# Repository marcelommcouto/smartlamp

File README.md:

# smartlamp
Projeto de lampada inteligente conectada a AWS

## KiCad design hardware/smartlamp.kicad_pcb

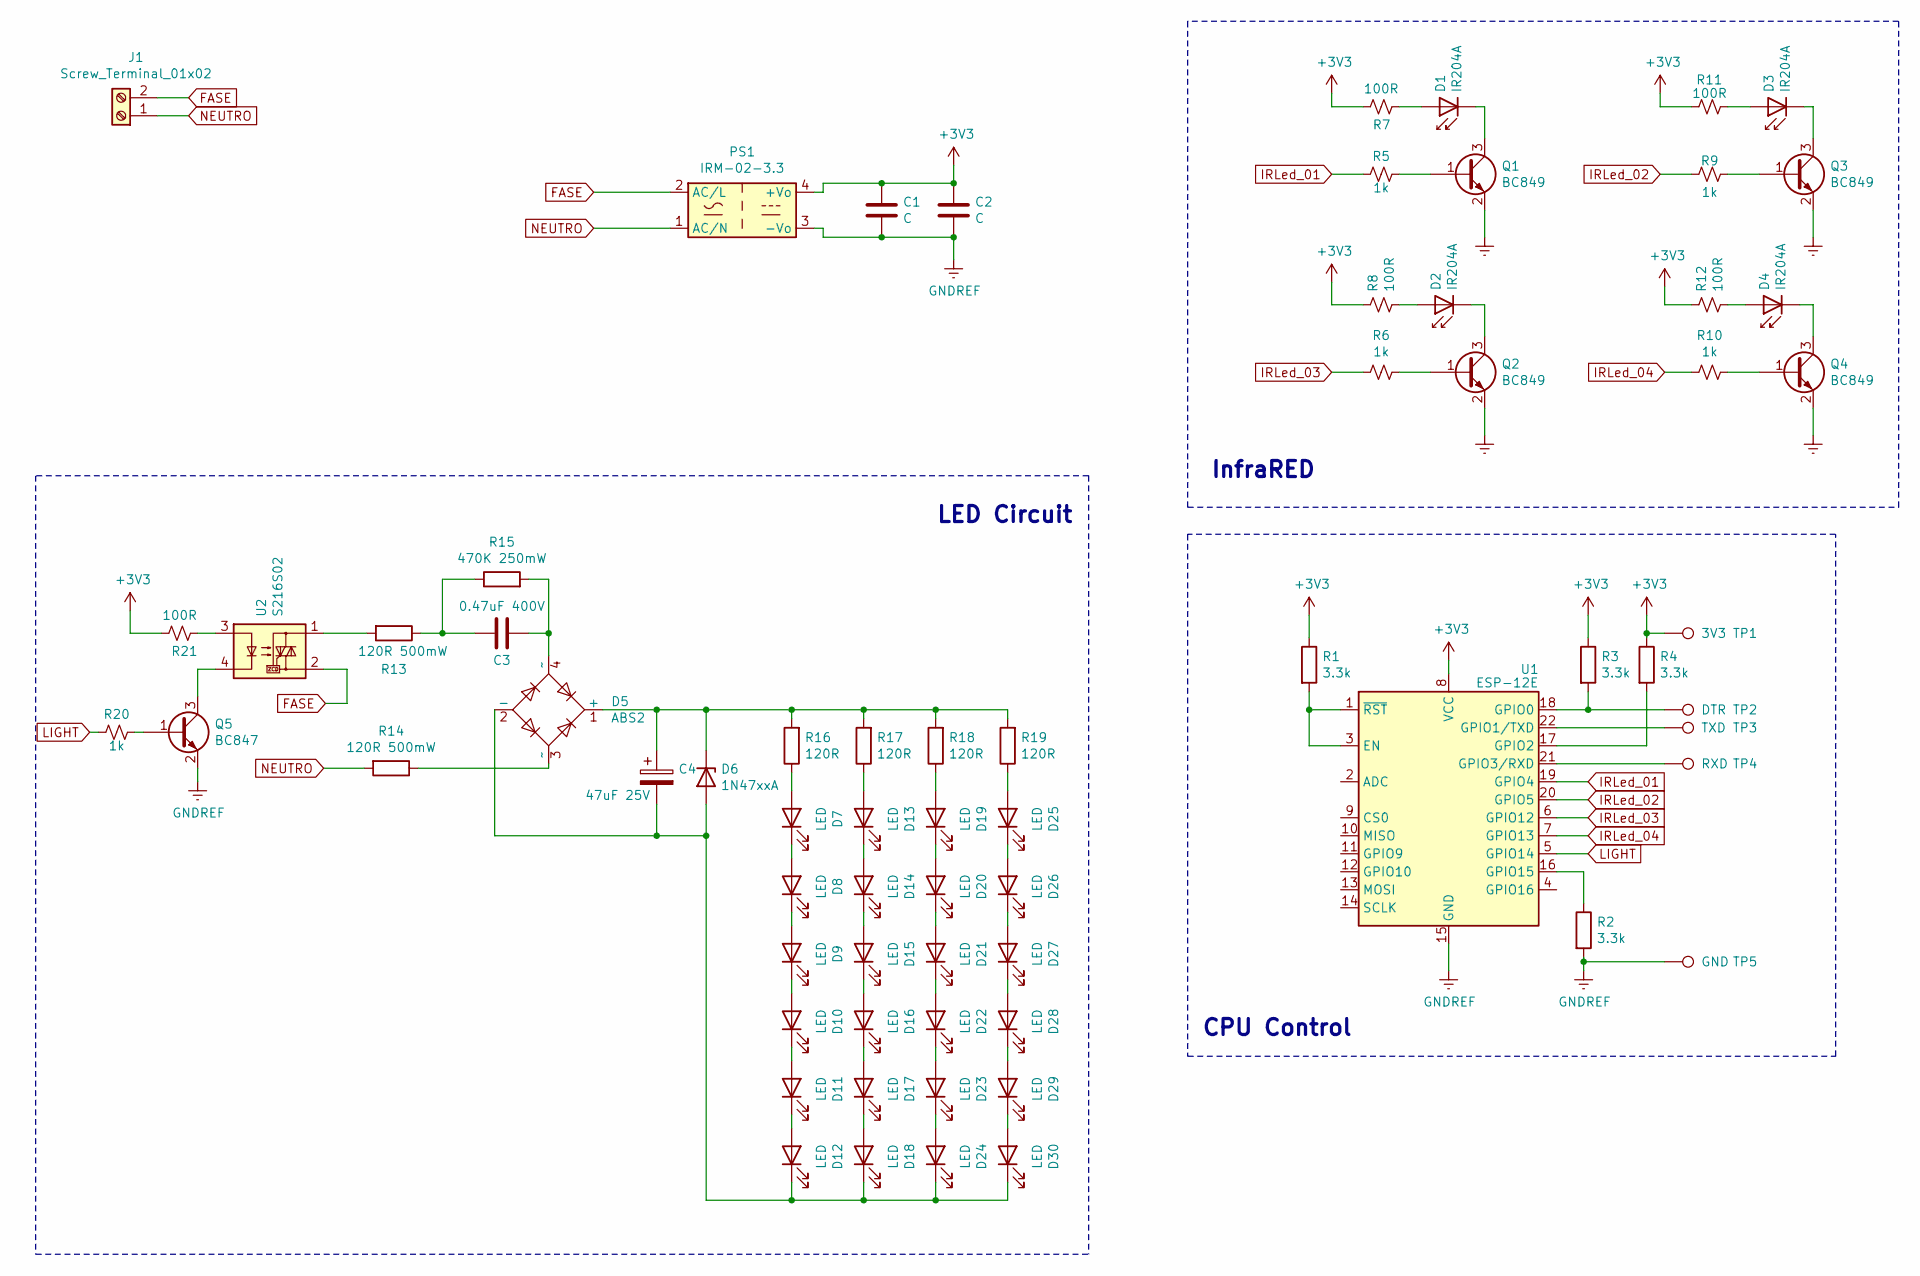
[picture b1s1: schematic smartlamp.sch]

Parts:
C1, C2: C; C_0805_2012Metric_Pad1.15x1.40mm_HandSolder
C3: 0.47uF 400V; C_Rect_L18.0mm_W8.0mm_P15.00mm_FKS3_FKP3
C4: 47uF 25V; C_Radial_D6.3mm_H11.0mm_P2.50mm
D1, D2, D3, D4: IR204A; LED_D3.0mm_IRBlack
D5: ABS2; Diode_Bridge_Diotec_ABS
D6: 1N47xxA; D_DO-41_SOD81_P10.16mm_Horizontal
D7, D8, D9, D10, D11, D12, D13, D14, D15, D16, D17, D18, D19, D20, D21, D22, D23, D24, D25, D26, D27, D28, D29, D30: LED; LED_1806_4516Metric
J1: Screw_Terminal_01x02; PhoenixContact_MCV_1,5_2-G-3.5_1x02_P3.50mm_Vertical
PS1: IRM-02-3.3; Converter_ACDC_MeanWell_IRM-02-xx_THT
Q1, Q2, Q3, Q4: BC849; SOT-23
Q5: BC847; SOT-23
R1, R2, R3, R4: 3.3k; C_0805_2012Metric_Pad1.15x1.40mm_HandSolder
R5, R6, R9, R10, R20: 1k; R_0805_2012Metric_Pad1.15x1.40mm_HandSolder
R7, R8, R11, R12, R21: 100R; R_0805_2012Metric_Pad1.15x1.40mm_HandSolder
R13, R14: 120R 500mW; R_1206_3216Metric_Pad1.42x1.75mm_HandSolder
R15: 470K 250mW; R_1206_3216Metric_Pad1.42x1.75mm_HandSolder
R16, R17, R18, R19: 120R; R_1206_3216Metric_Pad1.42x1.75mm_HandSolder
TP1: 3V3; TestPoint_Pad_D1.0mm
TP2: DTR; TestPoint_Pad_D1.0mm
TP3: TXD; TestPoint_Pad_D1.0mm
TP4: RXD; TestPoint_Pad_D1.0mm
TP5: GND; TestPoint_Pad_D1.0mm
U1: ESP-12E
U2: S216S02; SIP4_Sharp-SSR_P7.62mm_Straight

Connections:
+3V3: C1.1, C2.1, PS1.4 (+Vo), R1.1, R3.1, R4.1, R7.2, R8.1, R11.1, R12.1, R21.2, TP1.1, U1.8 (VCC)
FASE: J1.2, PS1.2 (AC/L), U2.2
GNDREF: C1.2, C2.2, PS1.3 (-Vo), Q1.2 (E), Q2.2 (E), Q3.2 (E), Q4.2 (E), Q5.2 (E), R2.2, TP5.1, U1.15 (GND)
IRLed_01: R5.2, U1.19 (GPIO4)
IRLed_02: R9.2, U1.20 (GPIO5)
IRLed_03: R6.2, U1.6 (GPIO12)
IRLed_04: R10.2, U1.7 (GPIO13)
LIGHT: R20.2, U1.5 (GPIO14)
NEUTRO: J1.1, PS1.1 (AC/N), R14.2
unnamed: C3.1, D5.4 (~~), R15.2
unnamed: C3.2, R13.1, R15.1
unnamed: C4.1, D5.1 (+), D6.1 (K), R16.2, R17.2, R18.2, R19.2
unnamed: C4.2, D5.2 (-), D6.2 (A), D12.1 (K), D18.1 (K), D24.1 (K), D30.1 (K)
unnamed: D1.1 (K), Q1.3 (C)
unnamed: D1.2 (A), R7.1
unnamed: D2.1 (K), Q2.3 (C)
unnamed: D2.2 (A), R8.2
unnamed: D3.1 (K), Q3.3 (C)
unnamed: D3.2 (A), R11.2
unnamed: D4.1 (K), Q4.3 (C)
unnamed: D4.2 (A), R12.2
unnamed: D5.3 (~~), R14.1
unnamed: D7.1 (K), D8.2 (A)
unnamed: D7.2 (A), R16.1
unnamed: D8.1 (K), D9.2 (A)
unnamed: D10.1 (K), D11.2 (A)
unnamed: D9.1 (K), D10.2 (A)
unnamed: D11.1 (K), D12.2 (A)
unnamed: D13.1 (K), D14.2 (A)
unnamed: D13.2 (A), R17.1
unnamed: D14.1 (K), D15.2 (A)
unnamed: D15.1 (K), D16.2 (A)
unnamed: D16.1 (K), D17.2 (A)
unnamed: D17.1 (K), D18.2 (A)
unnamed: D19.1 (K), D20.2 (A)
unnamed: D19.2 (A), R18.1
unnamed: D20.1 (K), D21.2 (A)
unnamed: D21.1 (K), D22.2 (A)
unnamed: D22.1 (K), D23.2 (A)
unnamed: D23.1 (K), D24.2 (A)
unnamed: D25.1 (K), D26.2 (A)
unnamed: D25.2 (A), R19.1
unnamed: D26.1 (K), D27.2 (A)
unnamed: D27.1 (K), D28.2 (A)
unnamed: D28.1 (K), D29.2 (A)
unnamed: D29.1 (K), D30.2 (A)
unnamed: Q1.1 (B), R5.1
unnamed: Q2.1 (B), R6.1
unnamed: Q3.1 (B), R9.1
unnamed: Q4.1 (B), R10.1
unnamed: Q5.1 (B), R20.1
unnamed: Q5.3 (C), U2.4
unnamed: R1.2, U1.1 (~RST), U1.3 (EN)
unnamed: R2.1, U1.16 (GPIO15)
unnamed: R3.2, TP2.1, U1.18 (GPIO0)
unnamed: R4.2, U1.17 (GPIO2)
unnamed: R13.2, U2.1
unnamed: R21.1, U2.3
unnamed: TP3.1, U1.22 (GPIO1/TXD)
unnamed: TP4.1, U1.21 (GPIO3/RXD)

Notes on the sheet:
CPU Control
InfraRED
LED Circuit

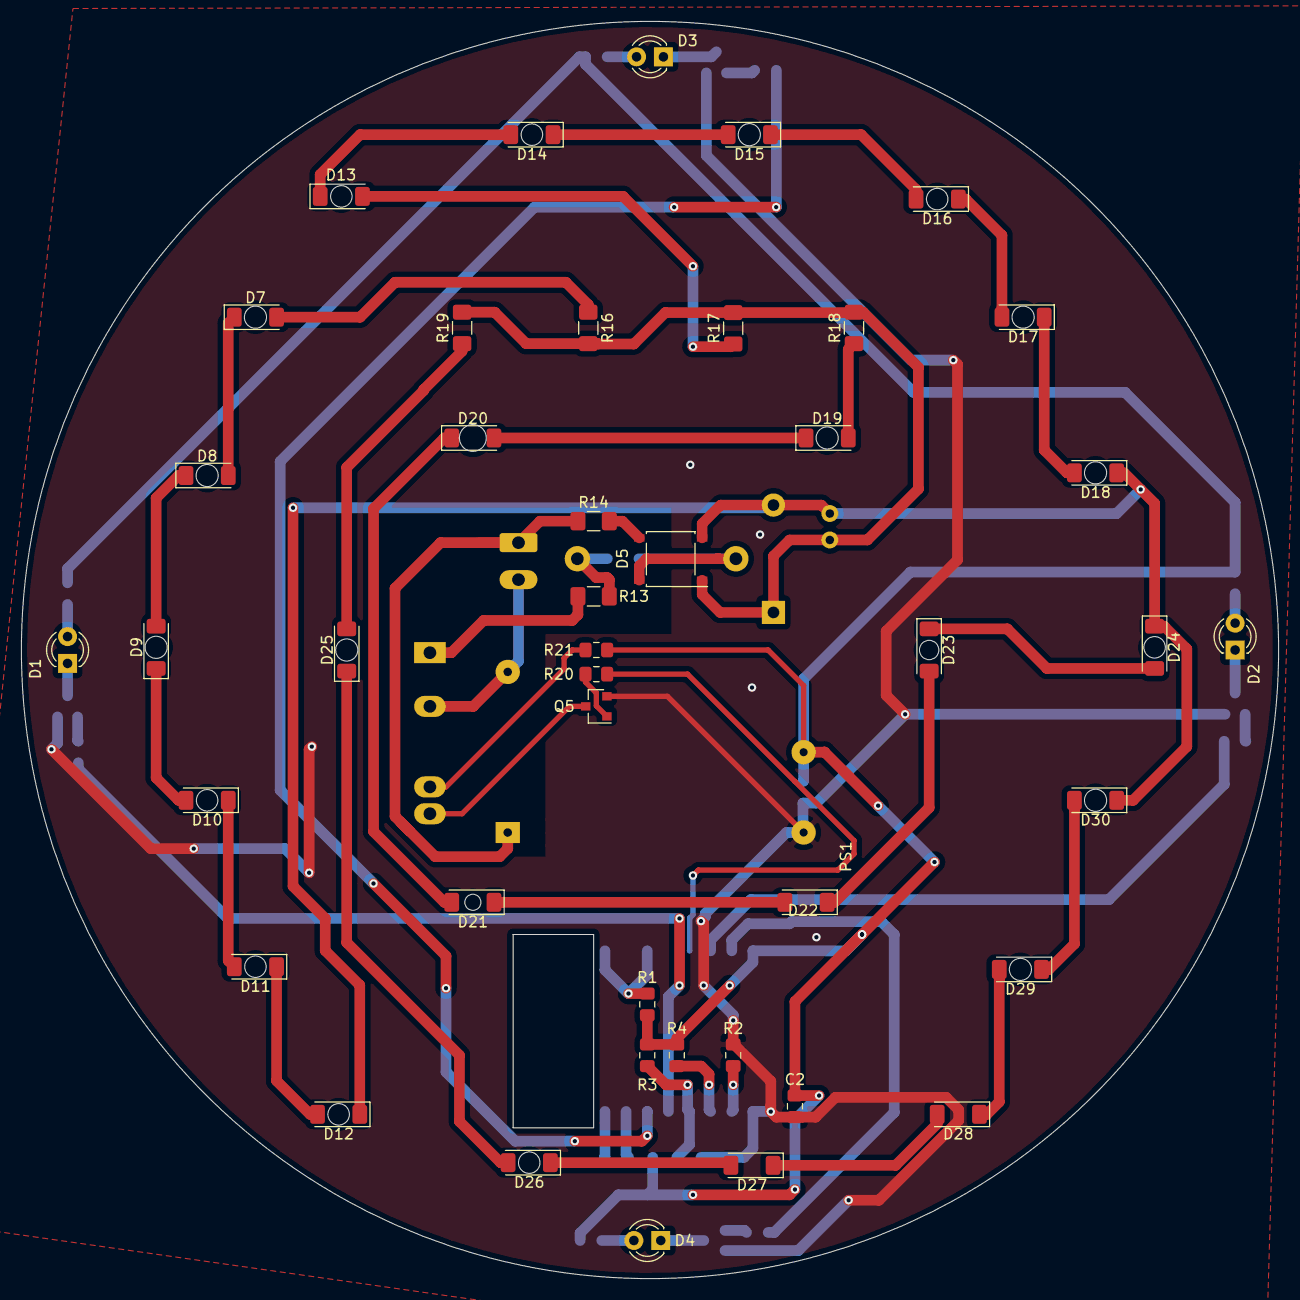
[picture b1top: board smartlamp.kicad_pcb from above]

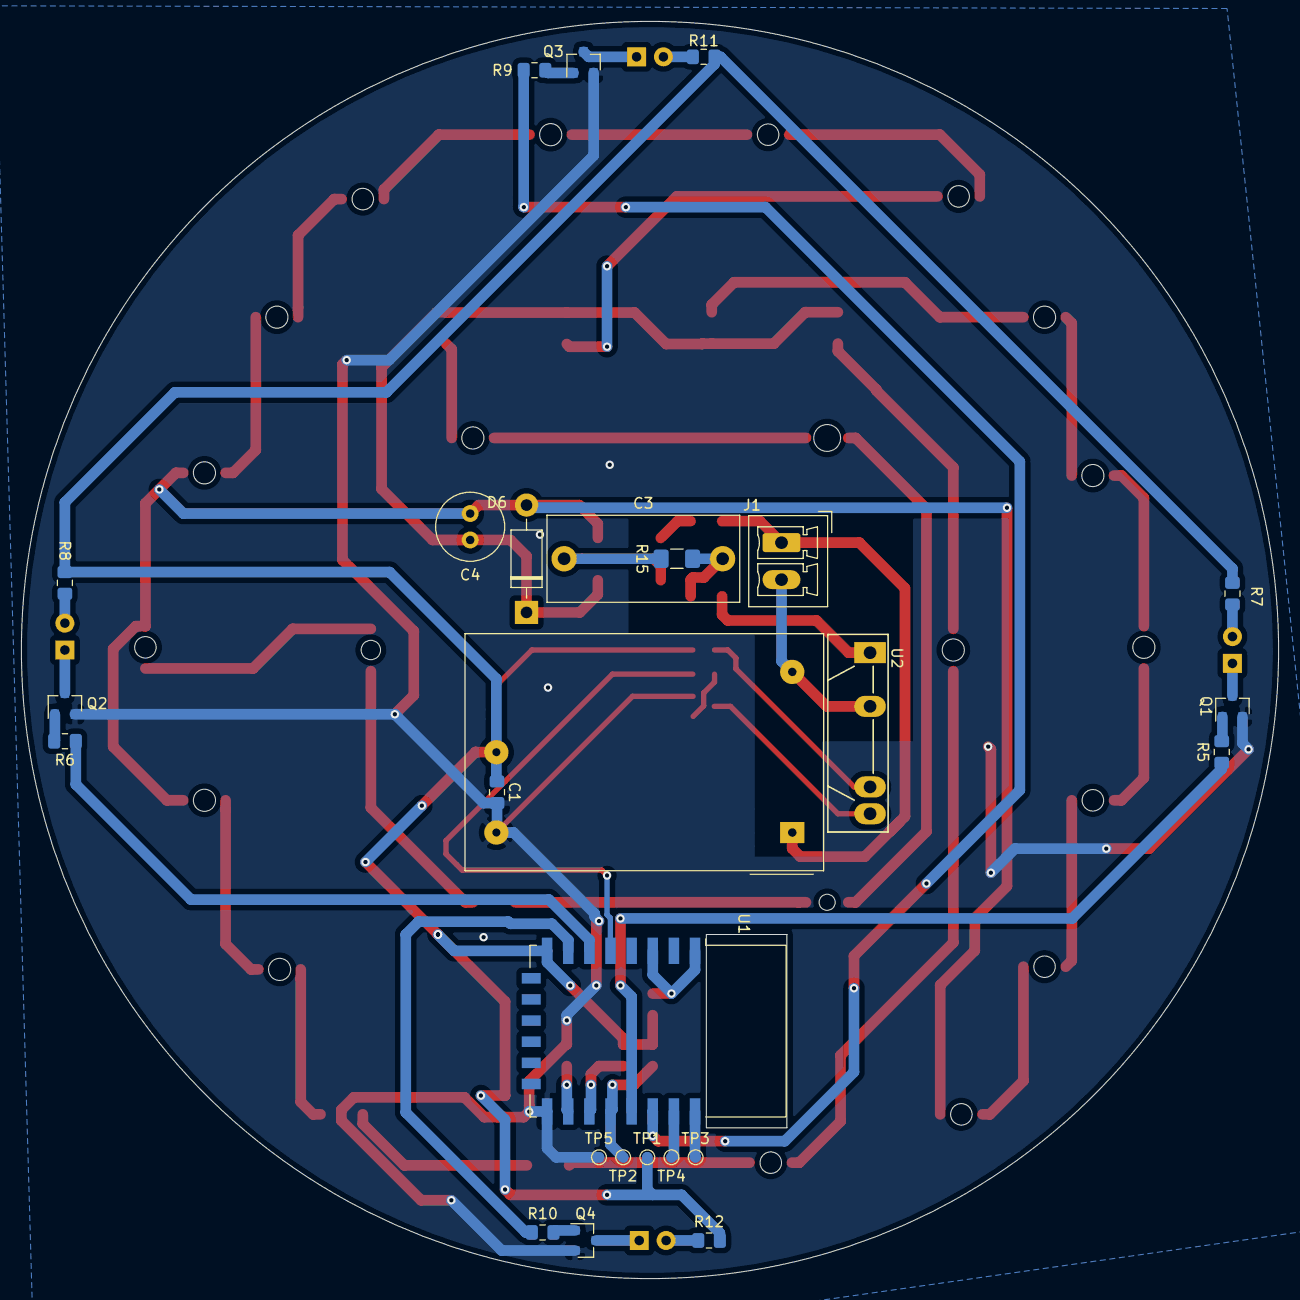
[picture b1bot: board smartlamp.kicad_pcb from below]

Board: 2 copper layers, 119.0 x 119.0 mm, 69 parts (26 on the bottom side), 60 nets.

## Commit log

2020-07-03 * Initial files
2020-07-10 * [Hardware] Adding solid state relay circuit to turn on/off lamp; * [Hardware] Routing all circuits added and selecting GPIO14 to control lamp; * [Firmware] Adding source code base to use SmartLamp 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
2020-07-10 * [Hardware] Updating hardware images;
